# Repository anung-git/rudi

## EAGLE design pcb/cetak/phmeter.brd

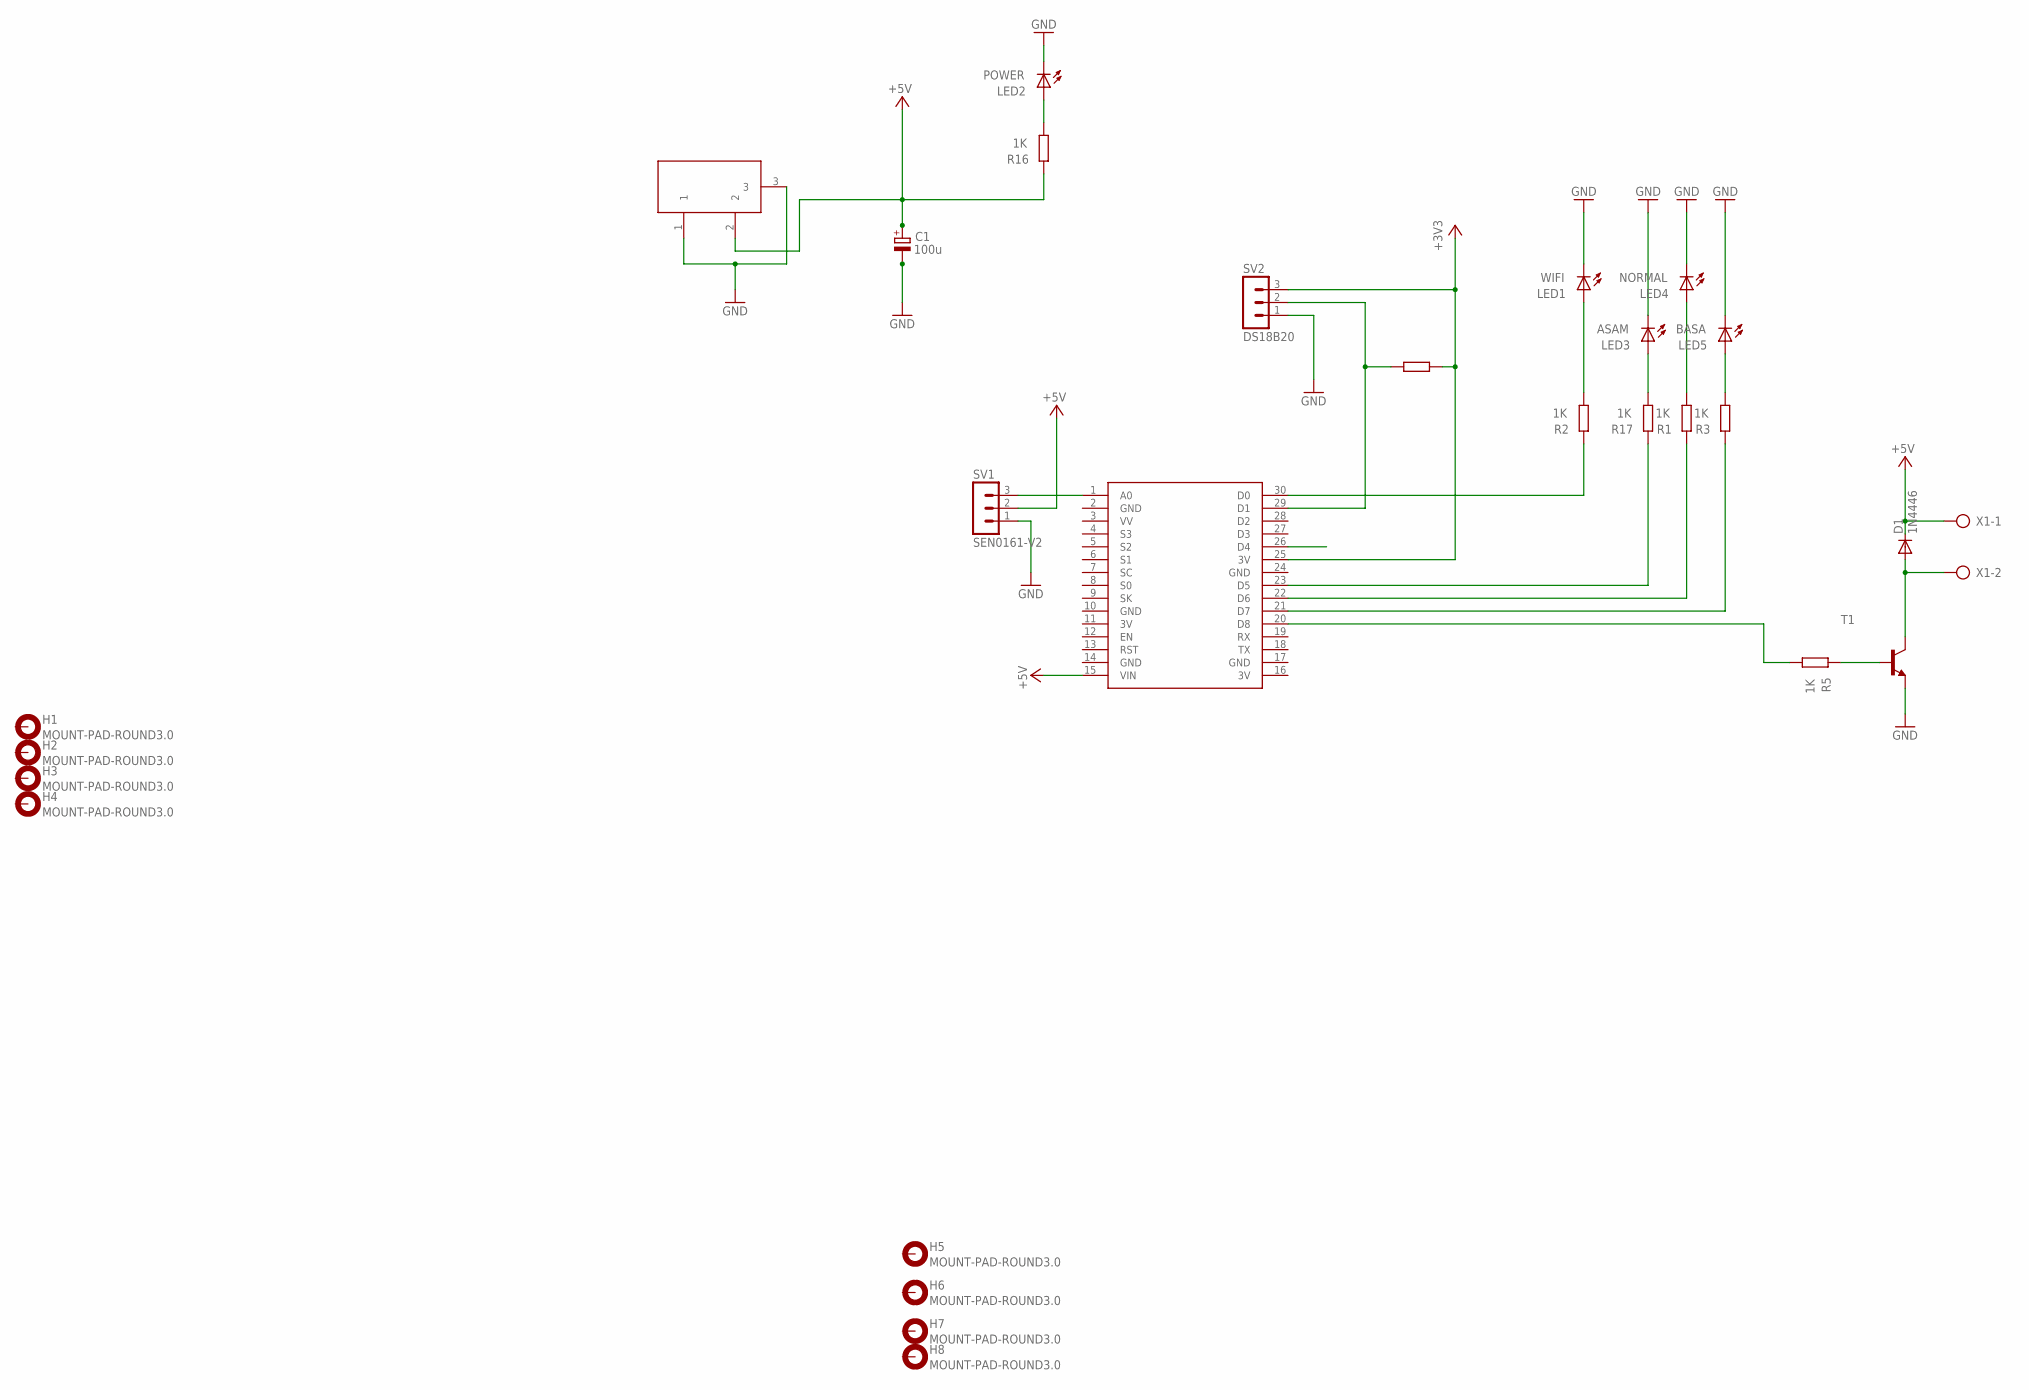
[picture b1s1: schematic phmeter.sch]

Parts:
C1: 100u; E3,5-8
D1: 1N4446; DO35-10
DC1: DC21MMX; DC-21MM
H1, H2, H3, H4, H5, H6, H7, H8: MOUNT-PAD-ROUND3.0; 3,0-PAD
LED1: WIFI; LED5MM
LED2: POWER; LED5MM
LED3: ASAM; LED5MM
LED4: NORMAL; LED5MM
LED5: BASA; LED5MM
R1, R2, R3, R5, R16, R17: 1K; 0207/10
R4: 1k; 0207/10
SV1: SEN0161-V2; MA03-1
SV2: DS18B20; MA03-1
T1: BC337-NPN-TO92-CBE; TO92-CBE
U$1: NODEMCU
X1: AK300/2

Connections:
3V: U$1.11 (3V), U$1.16 (3V)
+3V3: R4.1, SV2.3, U$1.25 (3V)
+5V: C1.+, D1.C, DC1.2, R16.2, SV1.2, U$1.15 (VIN), X1.1
GND: C1.-, DC1.1, DC1.3, LED1.K (C), LED2.K (C), LED3.K (C), LED4.K (C), LED5.K (C), SV1.1, SV2.1, T1.E, U$1.2 (GND), U$1.10 (GND), U$1.14 (GND), U$1.17 (GND), U$1.24 (GND)
unnamed: LED4.A, R1.1
unnamed: LED5.A, R3.1
unnamed: R1.2, U$1.22 (D6)
unnamed: R3.2, U$1.21 (D7)
unnamed: SV1.3, U$1.1 (A0)
unnamed: D1.A, T1.C, X1.2
unnamed: R5.2, T1.B
unnamed: R5.1, U$1.20 (D8)
unnamed: R4.2, SV2.2, U$1.29 (D1)
unnamed: R2.2, U$1.30 (D0)
unnamed: R17.2, U$1.23 (D5)
unnamed: LED2.A, R16.1
unnamed: LED3.A, R17.1
unnamed: LED1.A, R2.1

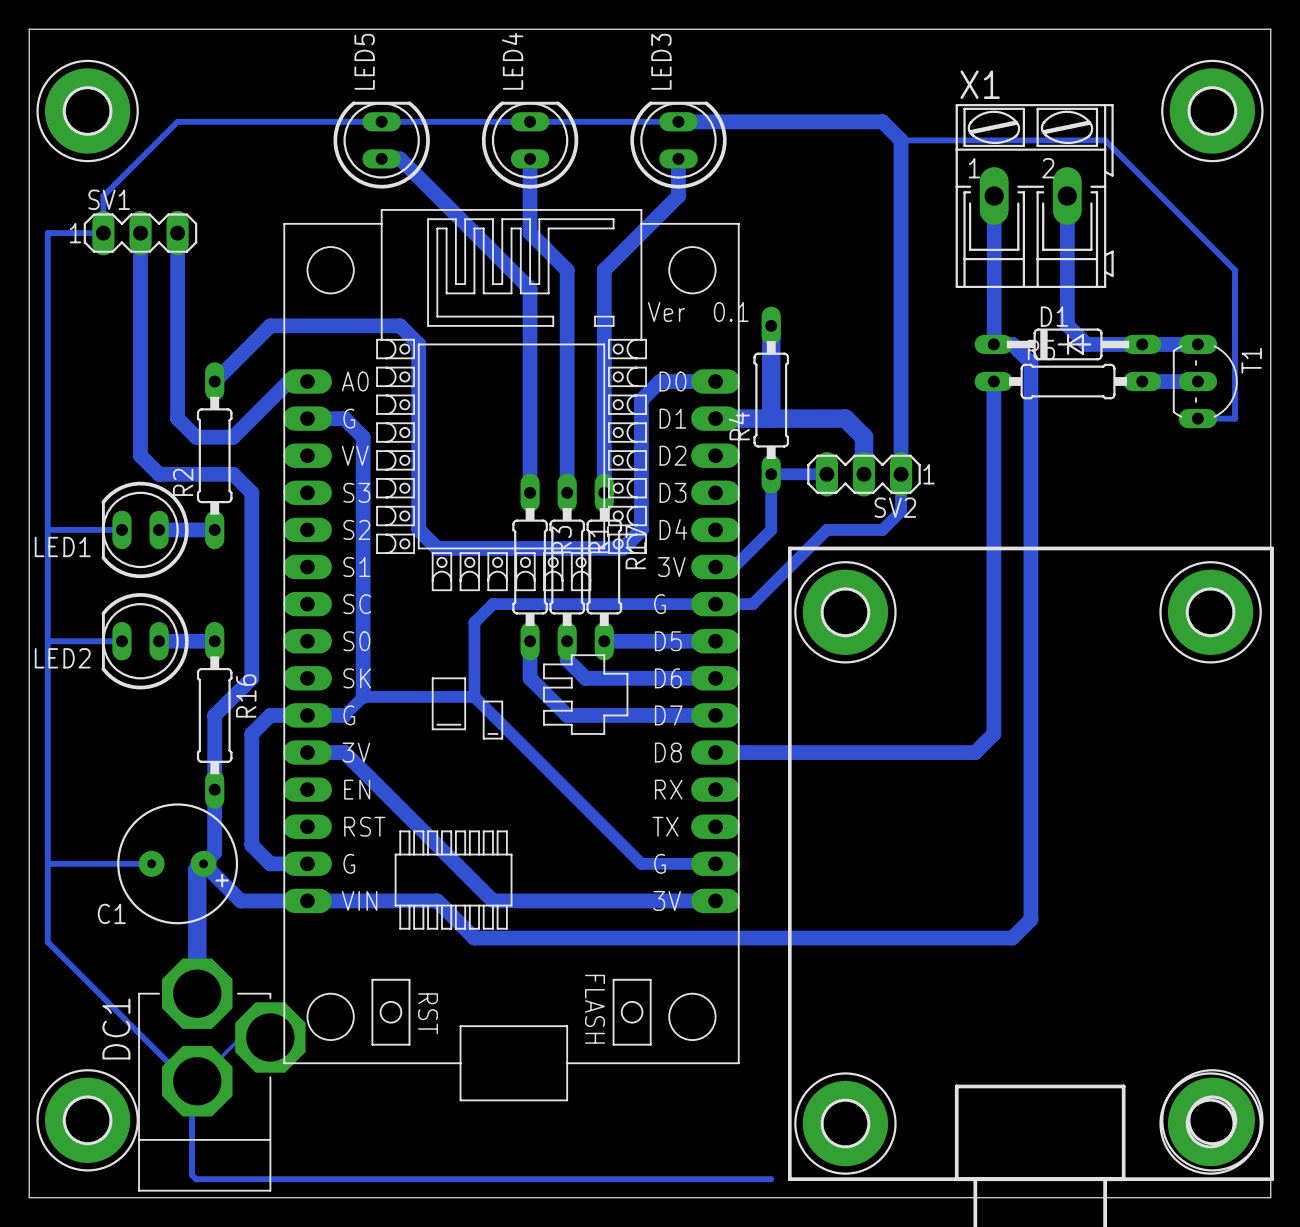
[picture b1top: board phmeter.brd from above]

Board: 2 copper layers, 85.0 x 80.0 mm, 28 parts (0 on the bottom side), 18 nets.

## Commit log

2020-07-09 upload
